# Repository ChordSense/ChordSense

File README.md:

# ChordSense

ChordSense combines a local Pi device interface with a separate companion website:

- **Attached-screen app:** `device-ui/` provides Play Along, Record, chord diagrams, playback controls and live feedback. It is a native Rust interface with no JavaScript or webview; its HTTP client calls `127.0.0.1:5051`.
- **Companion website:** `web/` is the Vercel song manager. A small discovery function finds the Pi's current Wi-Fi address from a short code; uploads, lists, downloads and deletes then go directly across the LAN.
- **Backend and hardware:** `backend/` retains API port **5051**; Rust `iod` owns ADC recording and DAC playback. Browser permissions cover pairing and the upload library only.
- **Optional analysis worker:** `backend/analysis_worker.py` can move whole-song/recording inference to another host. Live feedback remains local.

The companion replaces the Flask-rendered **`/upload` page formerly served on port 5051**. Vercel serves `/` and `/upload`; it does not host the Pi screen or proxy audio. The native screen retains bundled assets and offline device use.

## Pair a laptop or phone

The Pi publishes its current Wi-Fi address to the companion's short-lived discovery directory when **Pair uploads** starts. Entering the six-digit code finds that address automatically. There is no IP address in the website build, `.local` dependency, URL entry or network scan. Tailscale is for administrative SSH only; users need no Tailscale installation.

Tap **Pair uploads** on the updated Pi screen to generate a six-digit code, open the displayed website, enter the code and select **Pair device**. Allow local-network access if your browser asks. No device URL or long token needs to be typed.

Codes last 120 seconds, work once and close after five wrong attempts. A successful claim creates an eight-hour upload-only session for the current browser tab. Closing the Pi pairing dialog cancels an unused code; **Disconnect all** revokes every browser session. API restarts require pairing again.

The website lets every browser attempt a connection. HTTPS-to-local-HTTP behavior varies by browser, and Wi-Fi must allow peer communication. Allow browser local-network access if asked. Discovery uses HTTPS, but subsequent LAN HTTP does not encrypt pairing claims, tokens or audio. After the Pi's Wi-Fi IP changes, show a fresh code and pair again; existing sessions do not silently move to another address. No website redeployment is needed. See [connection requirements](docs/web-device-architecture.md#connection-options) and [browser test results](docs/browser-compatibility.md).

Automatic discovery is implemented locally but **not activated**: Upstash Marketplace terms acceptance and storage provisioning are pending, and this feature has not been deployed or copied to the Pi. It needs one backend source update, discovery environment settings and one API restart; the existing Pair uploads screen needs no rebuild, and `iod` needs no restart. See [the setup guide](docs/web-device-architecture.md#vercel-setup-from-the-local-working-directory), [Pi update steps](backend/deploy/README.md#activate-automatic-discovery-on-an-existing-pi) and [dated deployment record](docs/pi-pairing-deployment.md). Earlier browser results do not validate the new discovery flow.

## Prerequisites

- Git with submodule support.
- Python 3.10+ with `venv`; the optional Windows/Linux `setup.py` helper specifically requires Python 3.12.
- Rust/Cargo and native window/audio build libraries for the device screen; see [device prerequisites](device-ui/README.md#prerequisites).
- Node.js/npm only for the separate `web/` companion website.
- Linux audio tooling/development libraries, FFmpeg and the Pi's existing system HailoRT installation for Hailo inference.

## Clone the repository

For a fresh checkout:

```sh
git clone --recurse-submodules https://github.com/ChordSense/ChordSense.git
cd ChordSense
```

If an existing checkout has missing submodules, initialize them with `git submodule update --init --recursive`. Keep the current working branch when updating an existing project.

## Project structure

```text
ChordSense/
├── backend/                  # device API, model integration, optional worker
│   ├── deploy/               # API/worker configuration and deployment guides
│   └── models/               # separate model repositories/environments
├── device-ui/                # native Rust attached-screen app
├── web/                      # Vercel companion website
├── iod/                      # Pi ADC/DAC daemon
├── docs/
└── setup.py
```

## Backend setup

Use the Pi's existing compatible backend environment for updates. For a new developer environment, from `backend/`:

```sh
python3 -m venv .venv
.venv/bin/python -m pip install -r requirements.txt
```

`setup.py` uses `backend/.venv`; some existing manual installations use `backend/venv`. Match the real Python environment in the API launcher/service rather than creating another running process. The hardware deployment also needs the existing system Hailo bindings and `iod` socket configuration.

Configure the exact Vercel production origin in `CHORDSENSE_ALLOWED_ORIGINS`, and set `CHORDSENSE_COMPANION_URL` to that public website address displayed by the Pi. Set `CHORDSENSE_DISCOVERY_URL` to its `/api/discovery/publish` endpoint and share the private `CHORDSENSE_DISCOVERY_TOKEN` only between the Pi and Vercel function. The API listens on `0.0.0.0:5051` for LAN uploads; its native Rust client still uses loopback. Browser upload tokens are issued by pairing and are separate from this server publication secret.

## Model repository setup

The CNN-LSTM repository keeps a **separate Python environment** at `backend/models/chord-cnn-lstm-model/venv`. Its requirements and the reviewed `backend/patches/chord-model-compat.patch` are part of the existing model setup. For a fresh supported Windows/Linux installation, `python3.12 setup.py` initializes submodules, environments and the model compatibility patch. Existing installations should retain their model environments/checkpoints while updating the API/UI files.

The local custom CNN/Hailo recording path lives in `backend/models/chordsense_cnn/`. Optional worker inference uses CNN-LSTM and may produce different results. Do not assume the training environment is the same as the device API environment.

## Native Rust installation

Install Rust through [the official Rust instructions](https://rust-lang.org/tools/install/). On Windows use the MSVC toolchain and Microsoft C++ Build Tools with **Desktop development with C++**. The device screen no longer requires Tauri, WebView2, Node.js or npm. On Linux install the native window/audio libraries listed in [device-ui/README.md](device-ui/README.md#prerequisites). FFmpeg is used for pitch-preserving slower audio. After installing Rust, reload the terminal and check `cargo --version` and `rustc --version`.

## Build and run the native app

The installation helper builds the Rust interface and checks backend imports:

```sh
python setup.py
```

Use a Python 3.12 interpreter. The helper waits for backend health before opening the screen; it uses the backend virtual environment directly without shell activation. Use `python setup.py --no-launch` to install/build only or `python setup.py --windowed` to launch a development window. See [the device guide](device-ui/README.md) for manual Windows and Linux backend commands.

For a release build, from the repository root:

```sh
cargo build --release --locked --manifest-path device-ui/Cargo.toml
```

The executable is `device-ui/target/release/device-ui.exe` on Windows or `device-ui/target/release/device-ui` on Linux, unless Cargo's target directory is overridden. For development use:

```sh
cargo run --locked --manifest-path device-ui/Cargo.toml
```

Append `-- --windowed` for a window instead of fullscreen. Build the matching Linux/Pi artifact before updating the screen service. Existing Tauri service paths such as `src-tauri/target/...` must be changed to the native executable path. The [dated deployment record](docs/pi-pairing-deployment.md) describes the earlier Pi layout and is historical evidence, not the current build command. The [migration checklist](device-ui/MIGRATION.md) describes the remaining visual and hardware validation.

Start the matching backend separately with `python serve.py` from its configured environment, or restart its existing configured service. The helper reuses a healthy backend already on port 5051 and stops only a backend it launched itself when the screen closes. Use one API process; native hardware/session ownership is process-local. Follow [backend/deploy/README.md](backend/deploy/README.md) for environment loading and hostname setup. Remote companion sessions cannot record, play, seek, run live feedback or submit analysis jobs.

## Companion development and Vercel

From the repository root:

```sh
npm --prefix web run dev
npm --prefix web test
npm --prefix web run build
```

`npm run dev` previews the static interface at `http://127.0.0.1:5173/`; it does not run the HTTPS discovery function. Unit tests supply mocked discovery/device services. Test real automatic pairing through the configured HTTPS deployment and updated Pi backend.

Vercel uses the **repository root**: leave Root Directory blank, Framework Other, build `node web/scripts/build.mjs`, and clear any Output Directory override. The build keeps `web/dist` and emits static assets, a Node.js 22 discovery function and routing in `.vercel/output` using the [Build Output API](https://vercel.com/docs/build-output-api). The function generates the page's exact CSP from its discovered endpoint at request time. Remove `CHORDSENSE_API_URL`; builds reject that obsolete setting.

With a Vercel account, run `npx vercel@latest login` and `npx vercel@latest link` (project directory `./`). Provision the free Upstash store with automatic upgrades disabled, then set the server environment described in [the setup guide](docs/web-device-architecture.md#vercel-setup-from-the-local-working-directory). Build/test and deploy local files without a Git commit:

```sh
npm --prefix web test
npm --prefix web run build
npx vercel@latest deploy --prebuilt --prod
```

Vercel runtime settings are `UPSTASH_REDIS_REST_URL`/`UPSTASH_REDIS_REST_TOKEN` (or their `KV_REST_API_URL`/`KV_REST_API_TOKEN` aliases), `CHORDSENSE_DISCOVERY_TOKEN` and the exact `CHORDSENSE_COMPANION_ORIGIN`. Keep these server-side; neither Redis credentials nor the publication secret belongs in frontend assets. The old SSH preparation CLI is removed because the Pi publishes its address for each new pairing window.

## Pi efficiency and audio

`iod` sleeps without SPI reads while idle and wakes for capture/live streaming. Playback-speed renders are serialized with bounded FFmpeg threads. Uploaded-song analysis uses local `/analyze_uploaded` by filename instead of downloading/re-uploading a stored file. These changes reduce avoidable Pi work while the attached screen, DAC playback and live recognition remain local.

See [iod deployment](iod/deploy/README.md) for daemon builds/service configuration, [audio output](docs/audio-output.md) for the DAC path and troubleshooting, and [live-feedback implementation](docs/live-feedback-implementation-plan.md) for the recognizer. Updating Python does not update an installed daemon or native screen binary.

## Optional separate analysis host

Install `backend/requirements-worker.txt` into the worker HTTP environment and the model requirements into its separate model environment on another host. Use `backend/deploy/analysis-worker.env.example`, then run `python analysis_worker.py` from `backend/` behind HTTPS with a timeout suitable for inference. Set the Pi's `CHORDSENSE_ANALYSIS_URL` to its `/analyze` endpoint and match `CHORDSENSE_ANALYSIS_TOKEN` to the worker secret.

The worker serializes inference, caches results and deletes temporary inputs. The Pi streams files from disk. Configured worker failures preserve recordings and report failure without silently running expensive local inference. Leave worker configuration unset for local offline analysis; cached results remain useful. The companion website does not expose the worker or analysis jobs.

## Local verification

Use an intact backend environment with declared dependencies:

```sh
cd backend
.venv/bin/python -m unittest discover -s tests
```

Run `npm test` in `web/`, `cargo test --locked --manifest-path device-ui/Cargo.toml` from the repository root, and `cargo test --offline` in `iod/` when dependencies are cached. ADC tests use a mock reader rather than hardware. The [deployment record](docs/pi-pairing-deployment.md) records actual Pi backend tests and desktop Chrome LAN transfers. Android, native pairing-button input, capture pitch/duration, DAC output, live feedback and thermal performance require further device validation.

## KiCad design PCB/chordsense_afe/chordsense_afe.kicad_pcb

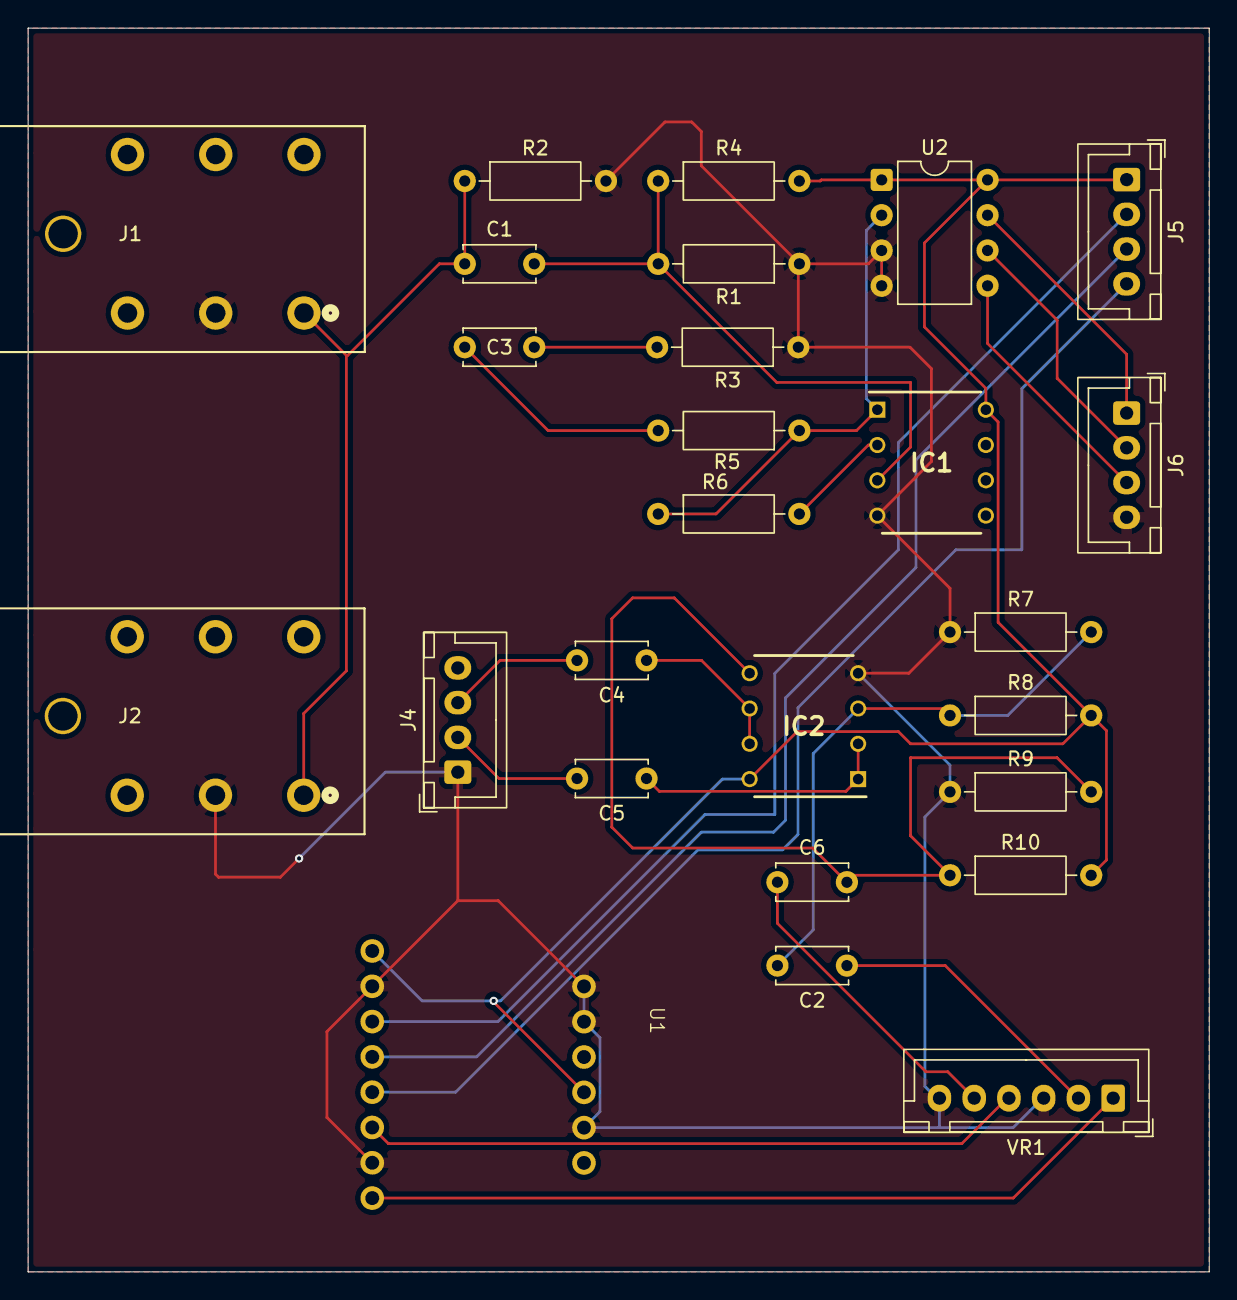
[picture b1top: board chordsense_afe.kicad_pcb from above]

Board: 2 copper layers, 85.0 x 89.5 mm, 26 parts (0 on the bottom side), 24 nets.

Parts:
C1, C2, C3, C4, C5, C6: C; C_Disc_D5.0mm_W2.5mm_P5.00mm
IC1, IC2: MCP6002-I_P; DIP781W56P254L950H533Q8N
J1, J2: ACJS-MHDR; CONN_MHDR_AMP
J4: SJ3-35053B; JST_XH_B4B-XH-A_1x04_P2.50mm_Vertical
J5, J6: Conn_01x04; JST_XH_B4B-XH-A_1x04_P2.50mm_Vertical
R1, R2, R3, R4, R5, R6, R7, R8, R9, R10: R; R_Axial_DIN0207_L6.3mm_D2.5mm_P10.16mm_Horizontal
U1: DAC
U2: MCP3201; DIP-8_W7.62mm
VR1: PDB182-K425K-103A; JST_XH_B6B-XH-A_1x06_P2.50mm_Vertical

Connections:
+3.3V: IC1.8 (VDD), IC2.8 (VDD), J5.1, R4.2, R8.2, R10.2, U1.1 (Vin), U1.12 (MU), U2.1 (Vref), U2.8 (Vdd)
/PI_BCK: J5.4, U1.5 (BCK)
/PI_CLK: J6.1, U2.7 (CLK)
/PI_CS: J6.3, U2.5 (~CS/SHDN)
/PI_Din: J5.3, U1.4 (Din)
/PI_Dout: J6.2, U2.6 (Dout)
/PI_wsel: J5.2, U1.3 (wsel)
GND: IC1.4 (VSS), IC2.4 (VSS), J1.2, J2.2, J4.1, J6.4, R1.1, R2.2, R3.1, R7.1, R9.1, U1.2 (GND), U1.7 (G), U1.9 (DE), U1.10 (FIL), U1.13 (FM), U2.3 (IN-), U2.4 (Vss), VR1.3 (R1_3), VR1.6 (R2_3)
unnamed: C1.1, J1.1, J2.1, R2.1
unnamed: C3.1, R5.2
unnamed: C3.2, R3.2
unnamed: C4.2, J4.3
unnamed: C5.2, J4.2
unnamed: C1.2, IC1.3 (VINA+), R1.2, R4.1
unnamed: IC1.2 (VINA-), R6.2
unnamed: IC1.1 (VOUTA), R5.1, R6.1, U2.2 (IN+)
unnamed: C2.2, IC2.3 (VINA+), R7.2, R8.1
unnamed: C5.1, IC2.1 (VOUTA), IC2.2 (VINA-)
unnamed: C6.2, IC2.5 (VINB+), R9.2, R10.1
unnamed: C4.1, IC2.6 (VINB-), IC2.7 (VOUTB)
unnamed: U1.6 (Lout), VR1.4 (R2_1)
unnamed: U1.8 (Rout), VR1.1 (R1_1)
unnamed: C2.1, VR1.2 (R1_2)
unnamed: C6.1, VR1.5 (R2_2)

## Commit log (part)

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2026-03-24 librosa code
2026-03-24 Initial config of dataset
2026-03-29 Complete initial CNN exploration notebook
2026-04-02 Added research documents, as well as initial plan of action
2026-04-02 fixed folder issues
2026-04-02 added model as submodule
2026-04-02 README updated
2026-04-02 README fixes
    Updated directory navigation commands for clarity.
2026-04-02 Revise model repository setup and dtype handling
    Update installation instructions and modify dtype in xhmm_ismir.py
2026-04-03 Update README with Jetson installation instructions
    Added instructions for Jetson users to uninstall and install specific versions of packages.
2026-04-05 Analog work pre-alpha
2026-04-05 embedded pre-alpha
2026-04-06 Added a new font and updated the ui rust app to have a cleaner design.
2026-04-06 Updated ui design of the Play Along mode.
2026-04-09 Latest model progress
2026-04-09 misc
2026-04-09 First commit, initial dataset processing
2026-04-09 Working model
2026-04-09 Completed smoothing and prepared skeleton for project structure
2026-04-09 new model integration skeleton
2026-04-09 changed clone cmd
2026-04-10 more integration
2026-04-10 small fix
2026-04-10 demo skeleton
2026-04-10 move guitar input
2026-04-11 endpoint definition, smoothing, initial chord recognition class
2026-04-11 added chord recognition and lab file generation, and incorporated into main application
2026-04-11 async guitar input and backend integration (wip)
2026-04-12 Designed ui for record mode and is currently set to a dummy .lab file for testing frontend with backend connection.
2026-04-14 demo fixes
2026-04-14 Fix formatting
2026-04-14 Companion App Research
2026-04-14 Revise ChordSense companion app research document
    Added key takeaways and organized research links for clarity.
